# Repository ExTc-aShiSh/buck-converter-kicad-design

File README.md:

# 🔽 Buck Converter PCB Design (KiCad)

This repository contains the complete **schematic and PCB design** of a **DC–DC buck (step-down) converter**, created using **KiCad**.  
The project demonstrates practical power electronics design, component selection, and PCB layout techniques.

---

## ⚡ Project Overview

A **buck converter** is a DC–DC switching regulator used to efficiently step down a higher input voltage to a lower output voltage.  
This design is suitable for learning, prototyping, and low-to-medium power applications.

---

## 🛠️ Tools Used

- **KiCad** – Schematic capture & PCB layout
- **KiCanvas** – Online viewing of design files

## 👀 View Design Online (No KiCad Needed)

You can **view the schematic and PCB layout online** using **KiCanvas**:

👉 **https://kicanvas.org**

Simply upload or paste the GitHub repository link into KiCanvas to explore the design interactively.

---

## 📌 Notes

- This design is intended for **educational and prototyping purposes**.
- Always verify component ratings and PCB clearances before fabrication.
- Test the circuit with proper protection and current-limited power supply.

---

## 📜 License

This project is licensed under the **MIT License** — feel free to use, modify, and distribute with attribution.

---

## 🤝 Contributions

Suggestions, improvements, and optimizations are welcome.  
Feel free to fork the repository and submit a pull request!

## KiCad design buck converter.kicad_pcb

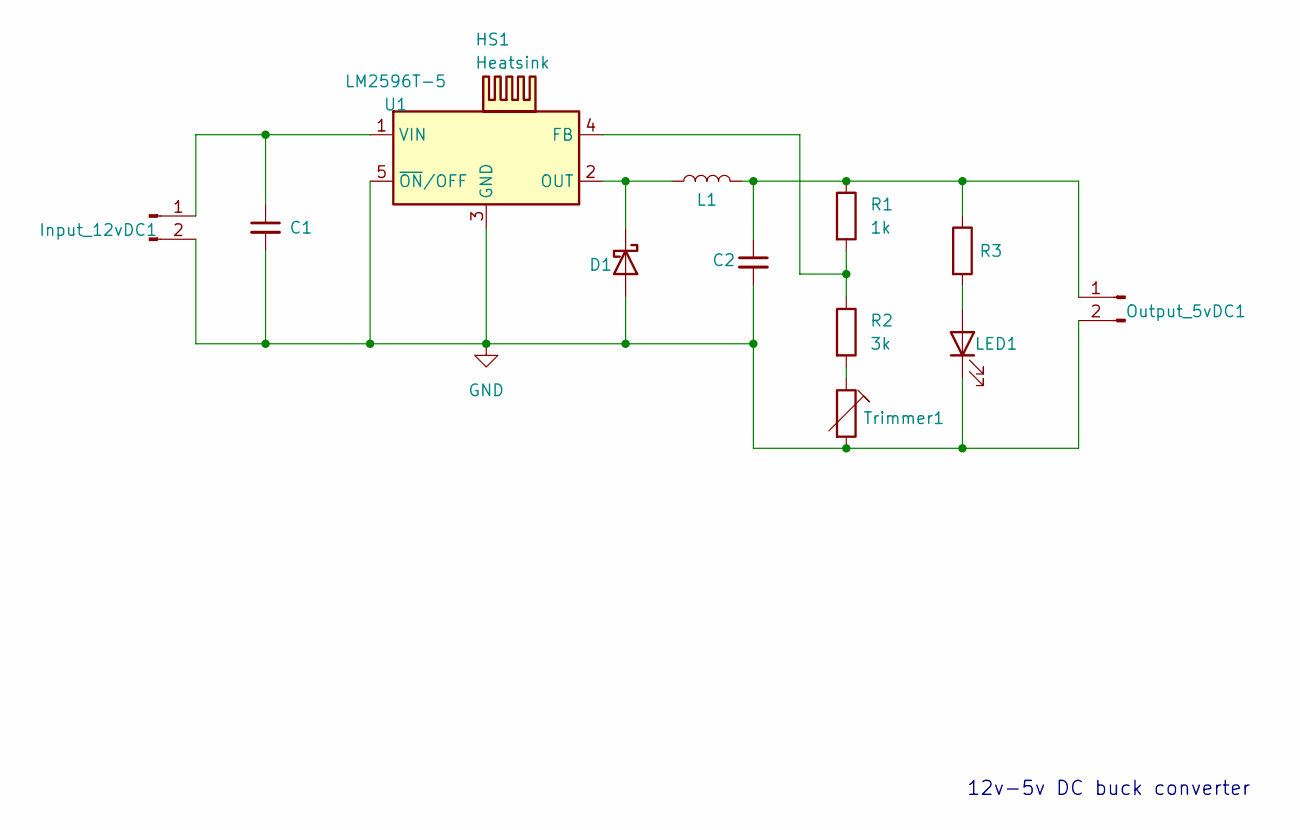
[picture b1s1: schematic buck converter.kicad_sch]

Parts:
C1: CP_Radial_D7.5mm_P2.50mm
C2: CP_Radial_D5.0mm_P2.50mm
D1: D_DO-41_SOD81_P10.16mm_Horizontal
HS1: Heatsink; Heatsink_TO220
Input_12vDC1: TerminalBlock_Phoenix_MPT-0,5-2-2.54_1x02_P2.54mm_Horizontal
L1: 68uH; L_Wurth_WE-LQSH-4020
LED1: LED_D3.0mm
Output_5vDC1: TerminalBlock_Phoenix_MPT-0,5-2-2.54_1x02_P2.54mm_Horizontal
R1: 1k; R_Axial_DIN0207_L6.3mm_D2.5mm_P10.16mm_Horizontal
R2: 3k; R_Axial_DIN0207_L6.3mm_D2.5mm_P10.16mm_Horizontal
R3: R_Axial_DIN0207_L6.3mm_D2.5mm_P7.62mm_Horizontal
Trimmer1: Potentiometer_Bourns_3296W_Vertical
U1: LM2596T-5; TO-220-5_P3.4x3.7mm_StaggerOdd_Lead3.8mm_Vertical

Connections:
GND: C1.2, C2.2, D1.2 (A), Input_12vDC1.2, LED1.1 (K), Output_5vDC1.2, Trimmer1.2, U1.3 (GND), U1.5 (~ON/OFF)
unnamed: D1.1 (K), L1.1, U1.2 (OUT)
unnamed: C1.1, Input_12vDC1.1, U1.1 (VIN)
unnamed: LED1.2 (A), R3.2
unnamed: C2.1, L1.2, Output_5vDC1.1, R1.1, R3.1
unnamed: R2.2, Trimmer1.1
unnamed: R1.2, R2.1, U1.4 (FB)

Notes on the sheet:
12v-5v DC buck converter

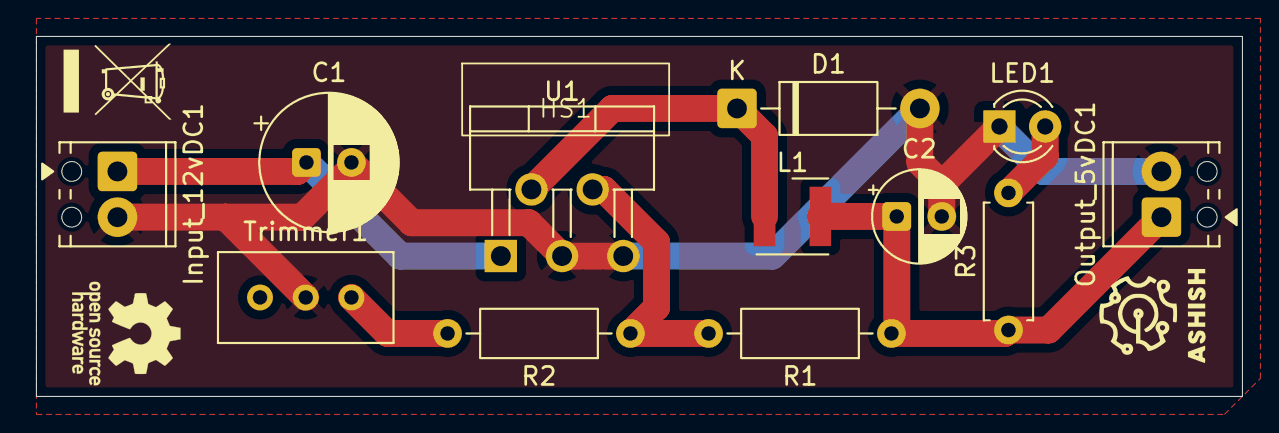
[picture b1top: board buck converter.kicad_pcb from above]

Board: 2 copper layers, 67.0 x 20.0 mm, 13 parts (0 on the bottom side), 7 nets.

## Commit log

2026-01-11 design files and screenshots are added
